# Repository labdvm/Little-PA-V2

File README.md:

# Little-PA-V2
Same as Little PA with few improvements

# Changes to this version:
- Added island around TCXO and under to isolate heating from the cooper for better temperature stability.
- Added few bigger vias for better ventilation.
- Added Bandpass filter to the TX for better RF isolation.
- Added bridge in case if used without PA, you can jump with two 0R resistors to get signal directly from the SX1255.
- -----------------------------------------------------
# Work with PA:
- R29 and R32 not soldered.
# Work without the PA:
- U4 and C28 not soldered, R29 and R32 soldered.

# Z32IT

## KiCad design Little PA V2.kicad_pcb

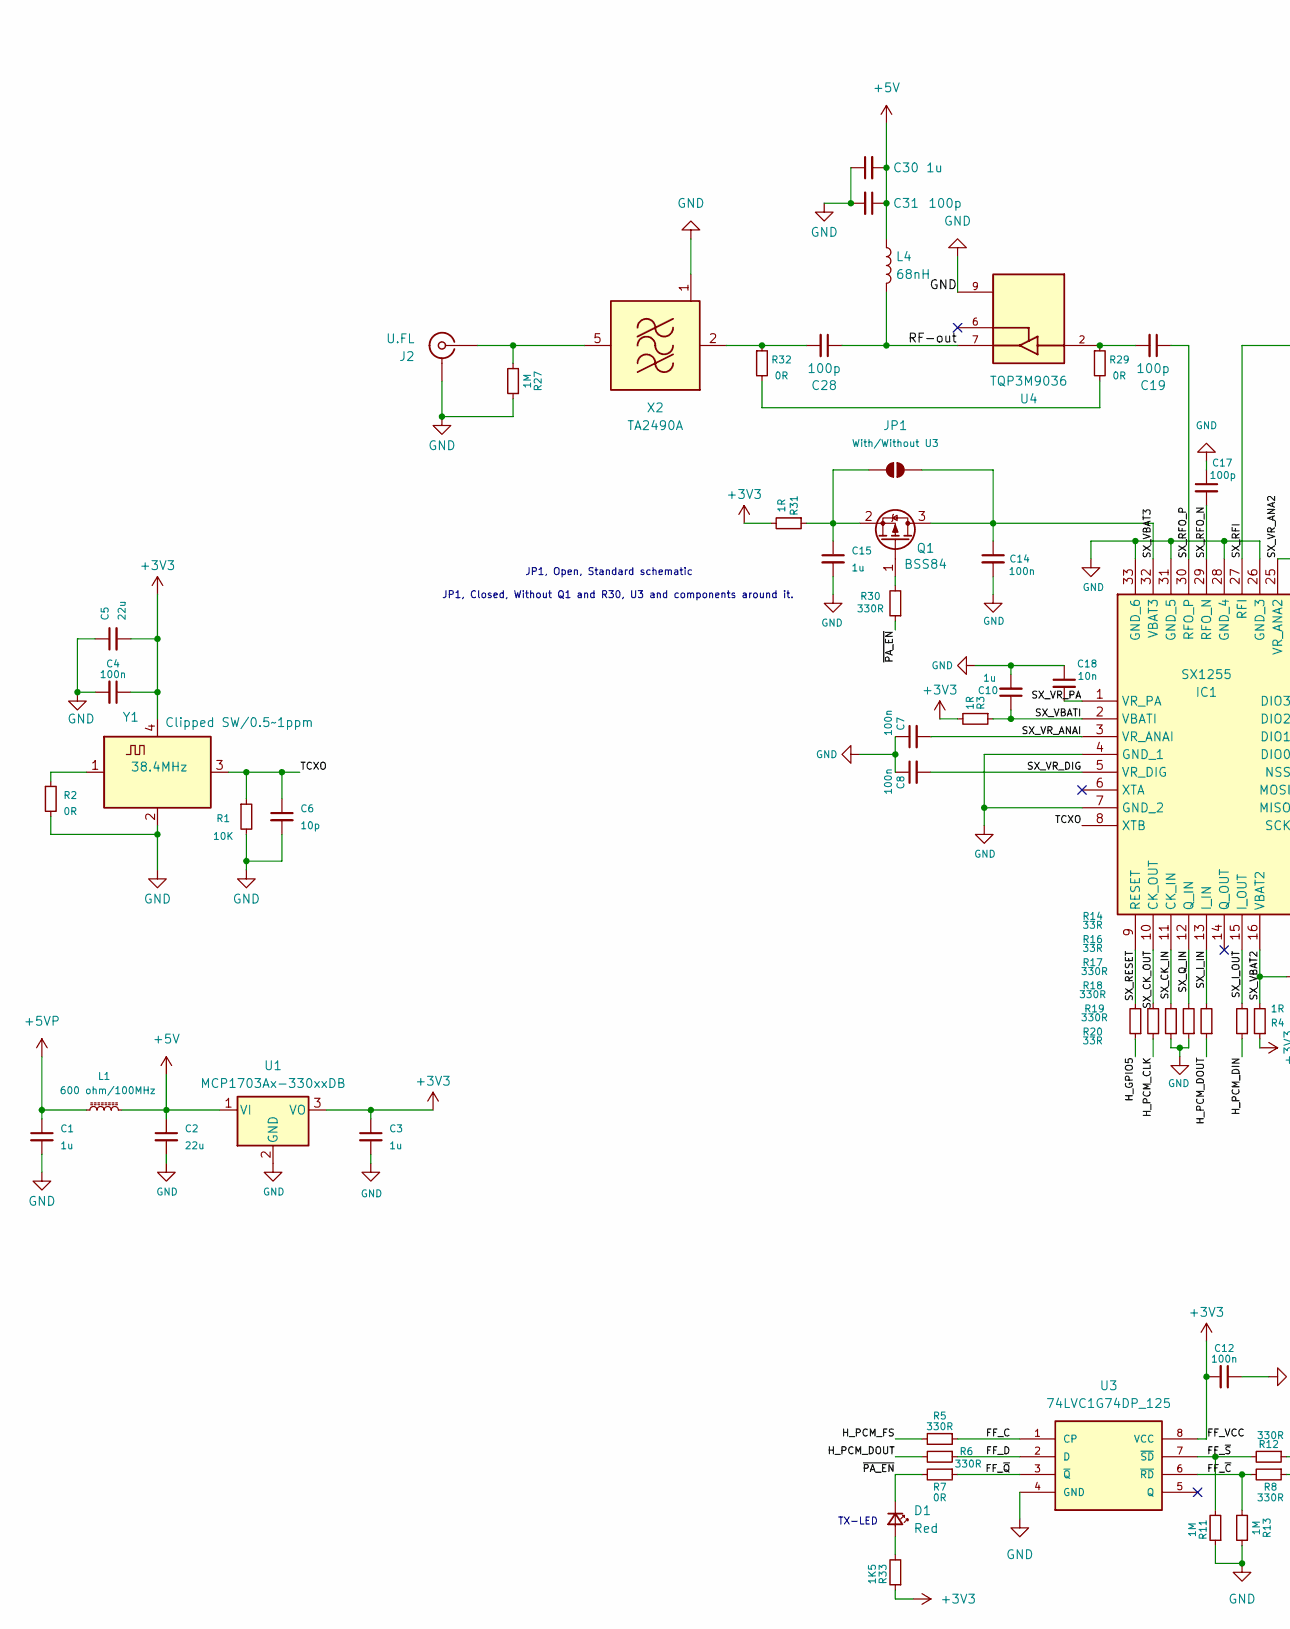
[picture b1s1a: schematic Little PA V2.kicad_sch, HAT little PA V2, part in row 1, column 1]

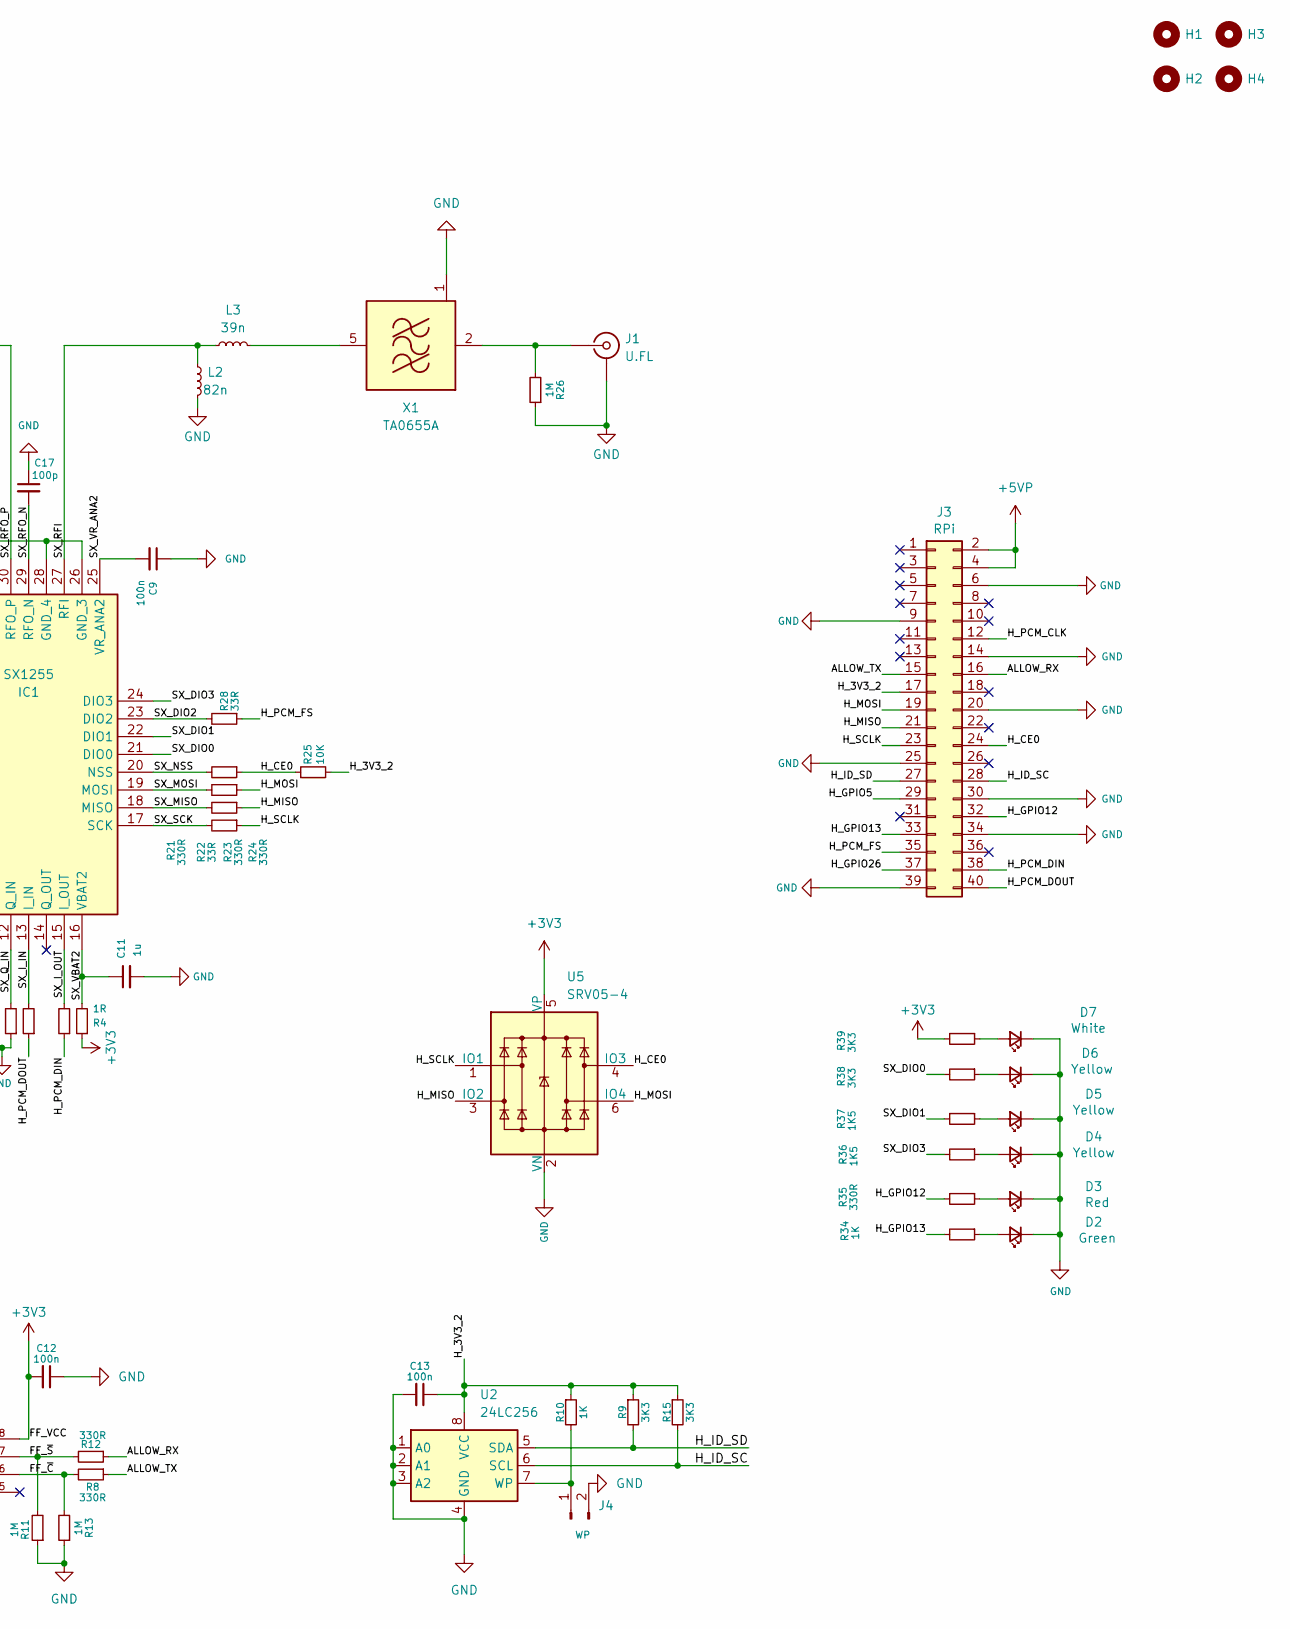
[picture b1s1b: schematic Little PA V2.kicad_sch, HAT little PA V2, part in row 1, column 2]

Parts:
C1, C3, C10, C11, C15, C30: 1u; C_0603_1608Metric; Part Number 311-3484-1-ND
C2, C5: 22u; C_0805_2012Metric; Part Number 1276-3148-1-ND
C4, C7, C8, C9, C12, C13, C14: 100n; C_0603_1608Metric; Part Number 720-1688-1-ND
C6: 10p; C_0603_1608Metric; Part Number 399-14932-1-ND
C17, C19, C28, C31: 100p; C_0603_1608Metric; Part Number 399-15348-1-ND
C18: 10n; C_0603_1608Metric; Part Number 399-C0603C103K8RACTUCT-ND
D1, D3: Red; LED_0603_1608Metric_Pad1.05x0.95mm_HandSolder; Part Number 160-1479-1-ND
D2: Green; LED_0603_1608Metric_Pad1.05x0.95mm_HandSolder; Part Number 754-APT1608SGD3CT-ND
D4, D5, D6: Yellow; LED_0603_1608Metric_Pad1.05x0.95mm_HandSolder; Part Number 160-1437-1-ND
D7: White; LED_0603_1608Metric_Pad1.05x0.95mm_HandSolder; Part Number 160-LTST-T180UWETCT-ND
H1, H2, H3, H4: MountingHole; MountingHole_2.7mm_M2.5_DIN965
IC1: SX1255; QFN50P500X500X80-33N-D; Part Number SX1255IWLTRTCT-ND
J1, J2: U.FL; Part Number 343-CONMHF1-SMD-G-TCT-ND
J3: RPi; PinSocket_2x20_P2.54mm_Vertical
J4: WP; PinHeader_1x02_P2.54mm_Vertical
JP1: With/Without U3; SolderJumper-2_P1.3mm_Open_RoundedPad1.0x1.5mm
L1: 600 ohm/100MHz; L_0805_2012Metric; Part Number 490-1046-1-ND
L2: 82n; L_0603_1608Metric; Part Number 712-LRC0603CJ82NGV001TCT-ND
L3: 39n; L_0603_1608Metric; Part Number 712-LRC0603CJ39NGV001TCT-ND
L4: 68nH; L_0603_1608Metric; Part Number 712-LRC0603CJ68NGV001TCT-ND
Q1: BSS84; SOT-23; Part Number 3372-BSS84TR-ND
R1, R25: 10K; R_0603_1608Metric; Part Number 541-10.0KHCT-ND
R2, R7, R29, R32: 0R; R_0603_1608Metric; Part Number 541-0.0GCT-ND
R3, R4, R31: 1R; R_0603_1608Metric; Part Number 541-1.00HHCT-ND
R5, R6, R8, R12, R17, R18, R19, R21, R23, R24, R30, R35: 330R; R_0603_1608Metric; Part Number 541-330HCT-ND
R9, R15, R38, R39: 3K3; R_0603_1608Metric; Part Number 541-3.30KHCT-ND
R10, R34: 1K; R_0603_1608Metric; Part Number 541-1.00KHCT-ND
R11, R13, R26, R27: 1M; R_0603_1608Metric; Part Number 541-1.00MHCT-ND
R14, R16, R20, R22, R28: 33R; R_0603_1608Metric; Part Number 541-33.0HCT-ND
R33, R36, R37: 1K5; R_0603_1608Metric; Part Number 541-1.5KGCT-ND
U1: MCP1703Ax-330xxDB; SOT-223-3_TabPin2; Part Number MCP1703T-3302E/DBCT-ND
U2: 24LC256; SOIC-8_3.9x4.9mm_P1.27mm; Part Number 24LC256-I/SN-ND
U3: 74LVC1G74DP_125; SOP65P400X110-8N; Part Number 1727-5983-1-ND
U4: TQP3M9036; SON50P200X200X95-9N; Part Number 2312-TQP3M9036CT-ND
U5: SRV05-4; SOT-23-6_Handsoldering; DigiKey Part Number SRV05-4CT-ND
X1: TA0655A; Filter_SAW-6_3.8x3.8mm
X2: TA2490A; Filter_SAW_Epcos_DCC6C_3x3mm
Y1: 38.4MHz; Crystal_SMD_3225-4Pin_3.2x2.5mm; Part Number 114-TG2520SMN38.4000M-MCGNNM3CT-ND

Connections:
+3V3: C3.1, C4.1, C5.2, C12.2, R3.2, R4.1, R31.2, R33.1, R39.2, U1.3 (VO), U3.8 (VCC), U5.5 (VP), Y1.4 (VDD)
+5V: C2.1, C30.2, C31.1, L1.2, L4.1, U1.1 (VI)
+5VP: C1.1, J3.2, J3.4, L1.1
/ALLOW_RX: J3.16, R12.1
/ALLOW_TX: J3.15, R8.1
/FF_C: R5.1, U3.1 (CP)
/FF_D: R6.1, U3.2 (D)
/FF_~C: R8.2, R13.2, U3.6 (~RD)
/FF_~Q: R7.1, U3.3 (~Q)
/FF_~S: R11.2, R12.2, U3.7 (~SD)
/H_3V3_2: C13.1, J3.17, R9.1, R10.1, R15.1, R25.2, U2.8 (VCC)
/H_CE0: J3.24, R24.1, R25.1, U5.4 (IO3)
/H_GPIO5: J3.29, R14.1
/H_GPIO12: J3.32, R35.2
/H_GPIO13: J3.33, R34.2
/H_GPIO26: J3.37
/H_ID_SC: J3.28, R15.2, U2.6 (SCL)
/H_ID_SD: J3.27, R9.2, U2.5 (SDA)
/H_MISO: J3.21, R22.1, U5.3 (IO2)
/H_MOSI: J3.19, R23.1, U5.6 (IO4)
/H_PCM_CLK: J3.12, R16.1
/H_PCM_DIN: J3.38, R20.1
/H_PCM_DOUT: J3.40, R6.2, R19.1
/H_PCM_FS: J3.35, R5.2, R28.1
/H_SCLK: J3.23, R21.1, U5.1 (IO1)
/RF-out: C28.1, L4.2, U4.7
/SX_CK_IN: IC1.11 (CK_IN), R17.2
/SX_CK_OUT: IC1.10 (CK_OUT), R16.2
/SX_DIO0: IC1.21 (DIO0), R38.2
/SX_DIO1: IC1.22 (DIO1), R37.2
/SX_DIO2: IC1.23 (DIO2), R28.2
/SX_DIO3: IC1.24 (DIO3), R36.2
/SX_I_IN: IC1.13 (I_IN), R19.2
/SX_I_OUT: IC1.15 (I_OUT), R20.2
/SX_MISO: IC1.18 (MISO), R22.2
/SX_MOSI: IC1.19 (MOSI), R23.2
/SX_NSS: IC1.20 (NSS), R24.2
/SX_Q_IN: IC1.12 (Q_IN), R18.2
/SX_RESET: IC1.9 (RESET), R14.2
/SX_RFI: IC1.27 (RFI), L2.2, L3.2
/SX_RFO_N: C17.2, IC1.29 (RFO_N)
/SX_RFO_P: C19.1, IC1.30 (RFO_P)
/SX_SCK: IC1.17 (SCK), R21.2
/SX_VBAT2: C11.1, IC1.16 (VBAT2), R4.2
/SX_VBAT3: C14.1, IC1.32 (VBAT3), JP1.2 (B), Q1.3 (D)
/SX_VBATI: C10.1, IC1.2 (VBATI), R3.1
/SX_VR_ANA2: C9.2, IC1.25 (VR_ANA2)
/SX_VR_ANAI: C7.2, IC1.3 (VR_ANAI)
/SX_VR_DIG: C8.2, IC1.5 (VR_DIG)
/SX_VR_PA: C18.2, IC1.1 (VR_PA)
/TCXO: C6.1, IC1.8 (XTB), R1.1, Y1.3 (OUT)
/~PA_EN: D1.1 (K), R7.2, R30.1
GND: C1.2, C2.2, C3.2, C4.2, C5.1, C6.2, C7.1, C8.1, C9.1, C10.2, C11.2, C12.1, C13.2, C14.2, C15.2, C17.1, C18.1, C30.1, C31.2, D2.1 (K), D3.1 (K), D4.1 (K), D5.1 (K), D6.1 (K), D7.1 (K), IC1.4 (GND_1), IC1.7 (GND_2), IC1.26 (GND_3), IC1.28 (GND_4), IC1.31 (GND_5), IC1.33 (GND_6), J1.2 (Ext), J2.2 (Ext), J3.6, J3.9, J3.14, J3.20, J3.25, J3.30, J3.34, J3.39, J4.2, L2.1, R1.2, R2.2, R11.1, R13.1, R17.1, R18.1, R26.1, R27.1, U1.2 (GND), U2.1 (A0), U2.2 (A1), U2.3 (A2), U2.4 (GND), U3.4 (GND), U4.9, U4.V1, U4.V2, U4.V3, U5.2 (VN), X1.1 (GND), X1.3 (GND), X1.4 (GND), X1.6 (GND), X2.1 (GND), X2.3 (GND), X2.4 (GND), X2.6 (GND), Y1.2 (GND)
unnamed: C19.2, R29.1, U4.2
unnamed: D1.2 (A), R33.2
unnamed: D2.2 (A), R34.1
unnamed: D3.2 (A), R35.1
unnamed: D4.2 (A), R36.1
unnamed: D5.2 (A), R37.1
unnamed: D6.2 (A), R38.1
unnamed: D7.2 (A), R39.1
unnamed: J1.1 (In), R26.2, X1.2 (IN)
unnamed: J2.1 (In), R27.2, X2.5 (OUT)
unnamed: J4.1, R10.2, U2.7 (WP)
unnamed: C15.1, JP1.1 (A), Q1.2 (S), R31.1
unnamed: Q1.1 (G), R30.2
unnamed: R29.2, R32.2
unnamed: L3.1, X1.5 (OUT)
unnamed: C28.2, R32.1, X2.2 (IN)
unnamed: R2.1, Y1.1 (Tri-State)

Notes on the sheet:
JP1, Closed, Without Q1 and R30, U3 and components around it.
JP1, Open, Standard schematic
TX-LED

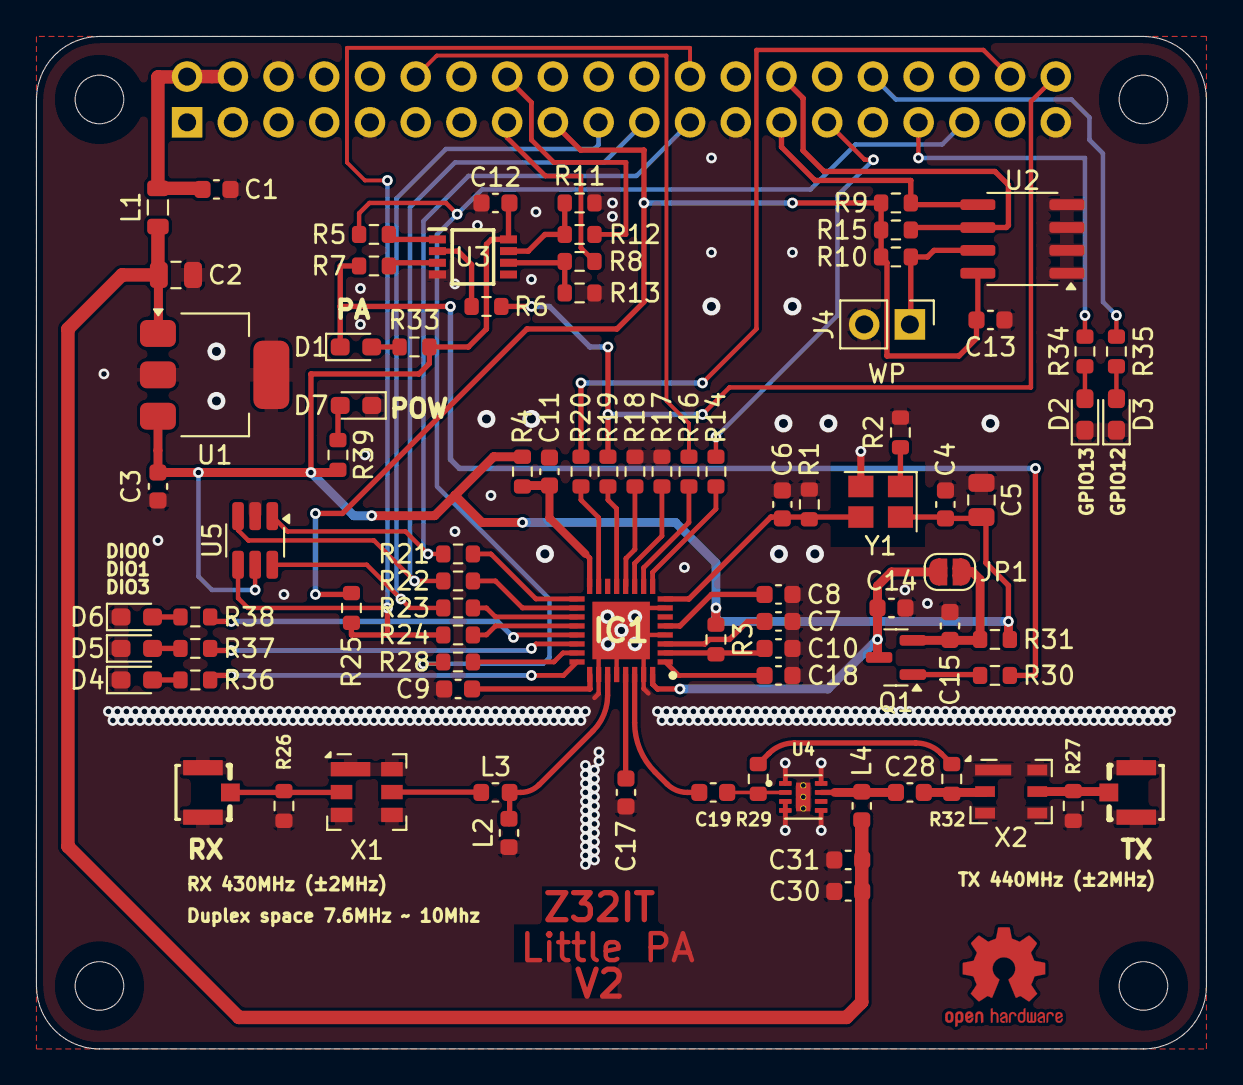
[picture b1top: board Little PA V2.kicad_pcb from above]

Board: 2 copper layers, 65.0 x 56.2 mm, 90 parts (1 on the bottom side), 69 nets.

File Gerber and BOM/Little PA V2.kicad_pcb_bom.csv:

Designator,Quantity,Value,Footprint,Package,MPN,DNP,Mount_Type,Manufacturer,Manufacturer Product Number,KiLib_Generator,Description,Sim.Pin,Height,PN,PROD_ID, Part Number,MANUFACTURER_NAME,MF,MOUSER_PRICE-STOCK,DESCRIPTION,MOUSER_PART_NUMBER,Price,Check_prices,HEIGHT,SnapEDA_Link,MP,Description_1,Availability,MANUFACTURER_PART_NUMBER,MAXIMUM_PACKAGE_HEIGHT,STANDARD,PARTREV,Purchase-URL,MANUFACTURER,Aliexpress,Model,TCXO-Footprints
"C1, C10, C11, C15, C3, C30",6,1u,C_0603_1608Metric,,,,smt,YAGEO,CC0603JRX7R6BB105,,,,,,,,,,,,,,,,,,,,,,,,,,,,
"C12, C13, C14, C4, C7, C8, C9",7,100n,C_0603_1608Metric,,,,smt,Vishay Vitramon,VJ0603Y104JXQPW1BC,,,,,,,,,,,,,,,,,,,,,,,,,,,,
"C17, C19, C28, C31",4,100p,C_0603_1608Metric,,,,smt,KEMET,C0603C101J8GACTU,,,,,,,,,,,,,,,,,,,,,,,,,,,,
C18,1,10n,C_0603_1608Metric,,,,smt,KEMET,C0603C103K8RACTU,,,,,,,,,,,,,,,,,,,,,,,,,,,,
"C2, C5",2,22u,C_0805_2012Metric,,1276-3148-1-ND,,smt,Samsung Electro-Mechanics,CL31B226MPHNNNE,SMD_2terminal_chip_molded,,,,,,,,,,,,,,,,,,,,,,,,,,,
C6,1,10p,C_0603_1608Metric,,,,smt,KEMET,C0603C100J8GACTU,,,,,,,,,,,,,,,,,,,,,,,,,,,,
D1,1,Red,LED_0603_1608Metric_Pad1.05x0.95mm_HandSolder,,160-1479-1-ND,,smt,Lite-On Inc.,LTST-S270KRKT,,"Light emitting diode, small symbol",1=K 2=A,,,,,,,,,,,,,,,,,,,,,,,,,
"D4, D5, D6",3,Yellow,LED_0603_1608Metric_Pad1.05x0.95mm_HandSolder,,160-1437-1-ND,,smt,Lite-On Inc.,LTST-C190KSKT,,"Light emitting diode, small symbol",1=K 2=A,,,,,,,,,,,,,,,,,,,,,,,,,
D7,1,White,LED_0603_1608Metric_Pad1.05x0.95mm_HandSolder,,160-LTST-T180UWETCT-ND,,smt,Lite-On Inc.,LTST-T180UWET,,"Light emitting diode, small symbol",1=K 2=A,,,,,,,,,,,,,,,,,,,,,,,,,
IC1,1,SX1255,QFN50P500X500X80-33N-D,,SX1255IWLTRT,,smt,Semtech Corporation,SX1255IWLTRT,,,,0.8,947-SX1255IWLTRT,,,,,,,,,,,,,,,,,,,,,,,
"J1, J2",2,U.FL,U.FL,,343-CONMHF1-SMD-G-TCT-ND,,smt,TE Connectivity Linx,CONMHF1-SMD-G-T,,,,,,CONN-09193,,,,,,,,,,,,,,,,,,,,,,
L1,1,600 ohm/100MHz,L_0805_2012Metric,,490-1046-1-ND,,smt,Murata Electronics,BLM21BD601SN1D,,FERRITE BEAD 600 OHM 0805 1LN,,,,,,,,,,,,,,,,,,,,,,,,,,
L2,1,82n,L_0603_1608Metric,,,,smt,Johanson Technology Inc.,LRC0603CJ82NGV001T,,,,,,,,,,,,,,,,,,,,,,,,,,,,
L3,1,39n,L_0603_1608Metric,,,,smt,Johanson Technology Inc.,LRC0603CJ39NGV001T,,,,,,,,,,,,,,,,,,,,,,,,,,,,
L4,1,68nH,L_0603_1608Metric,,,,smt,Johanson Technology Inc.,LRC0603CJ68NGV001T,,,,,,,712-LRC0603CJ68NGV001TCT-ND,,,,,,,,,,,,,,,,,,,,,
Q1,1,BSS84,SOT-23,,3372-BSS84TR-ND,,smt,MDD,BSS84,,,,,,,,,,,,,,,,,,,,,,,,,,,,
"R1, R25",2,10K,R_0603_1608Metric,,,,smt,Vishay Dale,CRCW060310K0FKEA,,,,,,,,,,,,,,,,,,,,,,,,,,,,
R10,1,1K,R_0603_1608Metric,,,,smt,Vishay Dale,CRCW06031K00FKEA,,,,,,,,,,,,,,,,,,,,,,,,,,,,
"R11, R13, R26, R27",4,1M,R_0603_1608Metric,,,,smt,Vishay Dale,CRCW06031M00FKEA,,,,,,,,,,,,,,,,,,,,,,,,,,,,
"R12, R17, R18, R19, R21, R23, R24, R30, R5, R6, R8",11,330R,R_0603_1608Metric,,,,smt,Vishay Dale,CRCW0603330RFKEA,,,,,,,,,,,,,,,,,,,,,,,,,,,,
"R14, R16, R20, R22, R28",5,33R,R_0603_1608Metric,,,,smt,Vishay Dale,CRCW060333R0FKEA,,,,,,,,,,,,,,,,,,,,,,,,,,,,
"R15, R38, R39, R9",4,3K3,R_0603_1608Metric,,,,smt,Vishay Dale,CRCW06033K30FKEA,,,,,,,,,,,,,,,,,,,,,,,,,,,,
"R2, R7",2,0R,R_0603_1608Metric,,,,smt,Vishay Dale,CRCW06030000Z0EA,,,,,,,,,,,,,,,,,,,,,,,,,,,,
"R3, R31, R4",3,1R,R_0603_1608Metric,,,,smt,Vishay Dale,CRCW06031R00FKEA,,,,,,,,,,,,,,,,,,,,,,,,,,,,
"R33, R36, R37",3,1K5,R_0603_1608Metric,,,,smt,Vishay Dale,CRCW06031K50JNEA,,,,,,,,,,,,,,,,,,,,,,,,,,,,
U1,1,MCP1703Ax-330xxDB,SOT-223-3_TabPin2,,MCP1703T-3302E/DBCT-ND,,smt,Microchip Technology,MCP1703T-3302E/DB,,,,,,,,,,,,,,,,,,,,,,,,,,,,
U2,1,24LC256,SOIC-8_3.9x4.9mm_P1.27mm,,24LC256-I/SN-ND,,smt,Microchip Technology,24LC256-I/SN,,,,,,,,,,,,,,,,,,,,,,,,,,,,
U3,1,74LVC1G74DP_125,SOP65P400X110-8N,TSSOP8-8 Nexperia USA Inc.,1727-5983-1-ND,,smt,Nexperia USA Inc.,"74LVC1G74DP,125",,,,,,,,Nexperia,NXP USA Inc.,https://www.mouser.co.uk/ProductDetail/Nexperia/74LVC1G74DP1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,74LVC1G74 - Single D-type flip-flop with set and reset; positive edge trigger@en-us,771-LVC1GDP125,None,"https://www.snapeda.com/parts/74LVC1G74DP,125/NXP+Semiconductors/view-part/?ref=eda",1.1mm,"https://www.snapeda.com/parts/74LVC1G74DP,125/NXP+Semiconductors/view-part/?ref=snap","74LVC1G74DP,125","Flip Flop 1 Element D-Type 1 Bit Positive Edge 8-TSSOP, 8-MSOP (0.118, 3.00mm Width)",In Stock,"74LVC1G74DP,125",,,,,,,,
U4,1,TQP3M9036,SON50P200X200X95-9N,DFN-8 Qorvo,2312-TQP3M9036CT-ND,,smt,Qorvo,TQP3M9036,,,,,,,,,Qorvo,,,,None,https://www.snapeda.com/parts/TQP3M9036/Qorvo/view-part/?ref=eda,,https://www.snapeda.com/parts/TQP3M9036/Qorvo/view-part/?ref=snap,TQP3M9036,RF Amp Chip Single GP 2GHz 5.25V 8-Pin DFN EP T/R,In Stock,,0.95mm,IPC-7351B,N/A,https://www.snapeda.com/api/url_track_click_mouser/?unipart_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,Qorvo,,,
X1,1,TA0655A,Filter_SAW-6_3.8x3.8mm,,,,smt,,,,"Bandpass Filter, 430MHz, BW-4MHz",,,,,,,,,,,,,,,,,,,,,,,,https://www.aliexpress.com/item/1005011831789075.html?pdp_ex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,,
X2,1,TA2490A,Filter_SAW_Epcos_DCC6C_3x3mm,,,,smt,,,,"Bandpass Filter, 440MHz, BW-2MHz",,,,,,,,,,,,,,,,,,,,,,,,https://www.aliexpress.com/item/1005011831747244.html?pdp_ex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,,
Y1,1,38.4MHz,Crystal_SMD_3225-4Pin_3.2x2.5mm,,114-TG2520SMN38.4000M-MCGNNM3CT-ND,,smt,EPSON ,TG2520SMN 38.4000M-MCGNNM3,,Clipped SW/0.5~1ppm,,,,,,,,,,,,,,,,,,,,,,,,,KDS-DSB321SDN or other brands,3225 or 2510

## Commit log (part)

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2026-06-02 Update README with changes for Little-PA-V2
    Document improvements and changes in Little-PA-V2.
2026-06-03 Update README with PA usage instructions
    Clarified instructions for working with and without PA.
2026-06-18 Enhance README with ordering details and version changes
    Updated README to include ordering information and changes in version.
